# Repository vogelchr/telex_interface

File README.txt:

PCB to implement the interface described here:

https://github.com/fablab-wue/piTelex/wiki/SW_DevRPiTTY

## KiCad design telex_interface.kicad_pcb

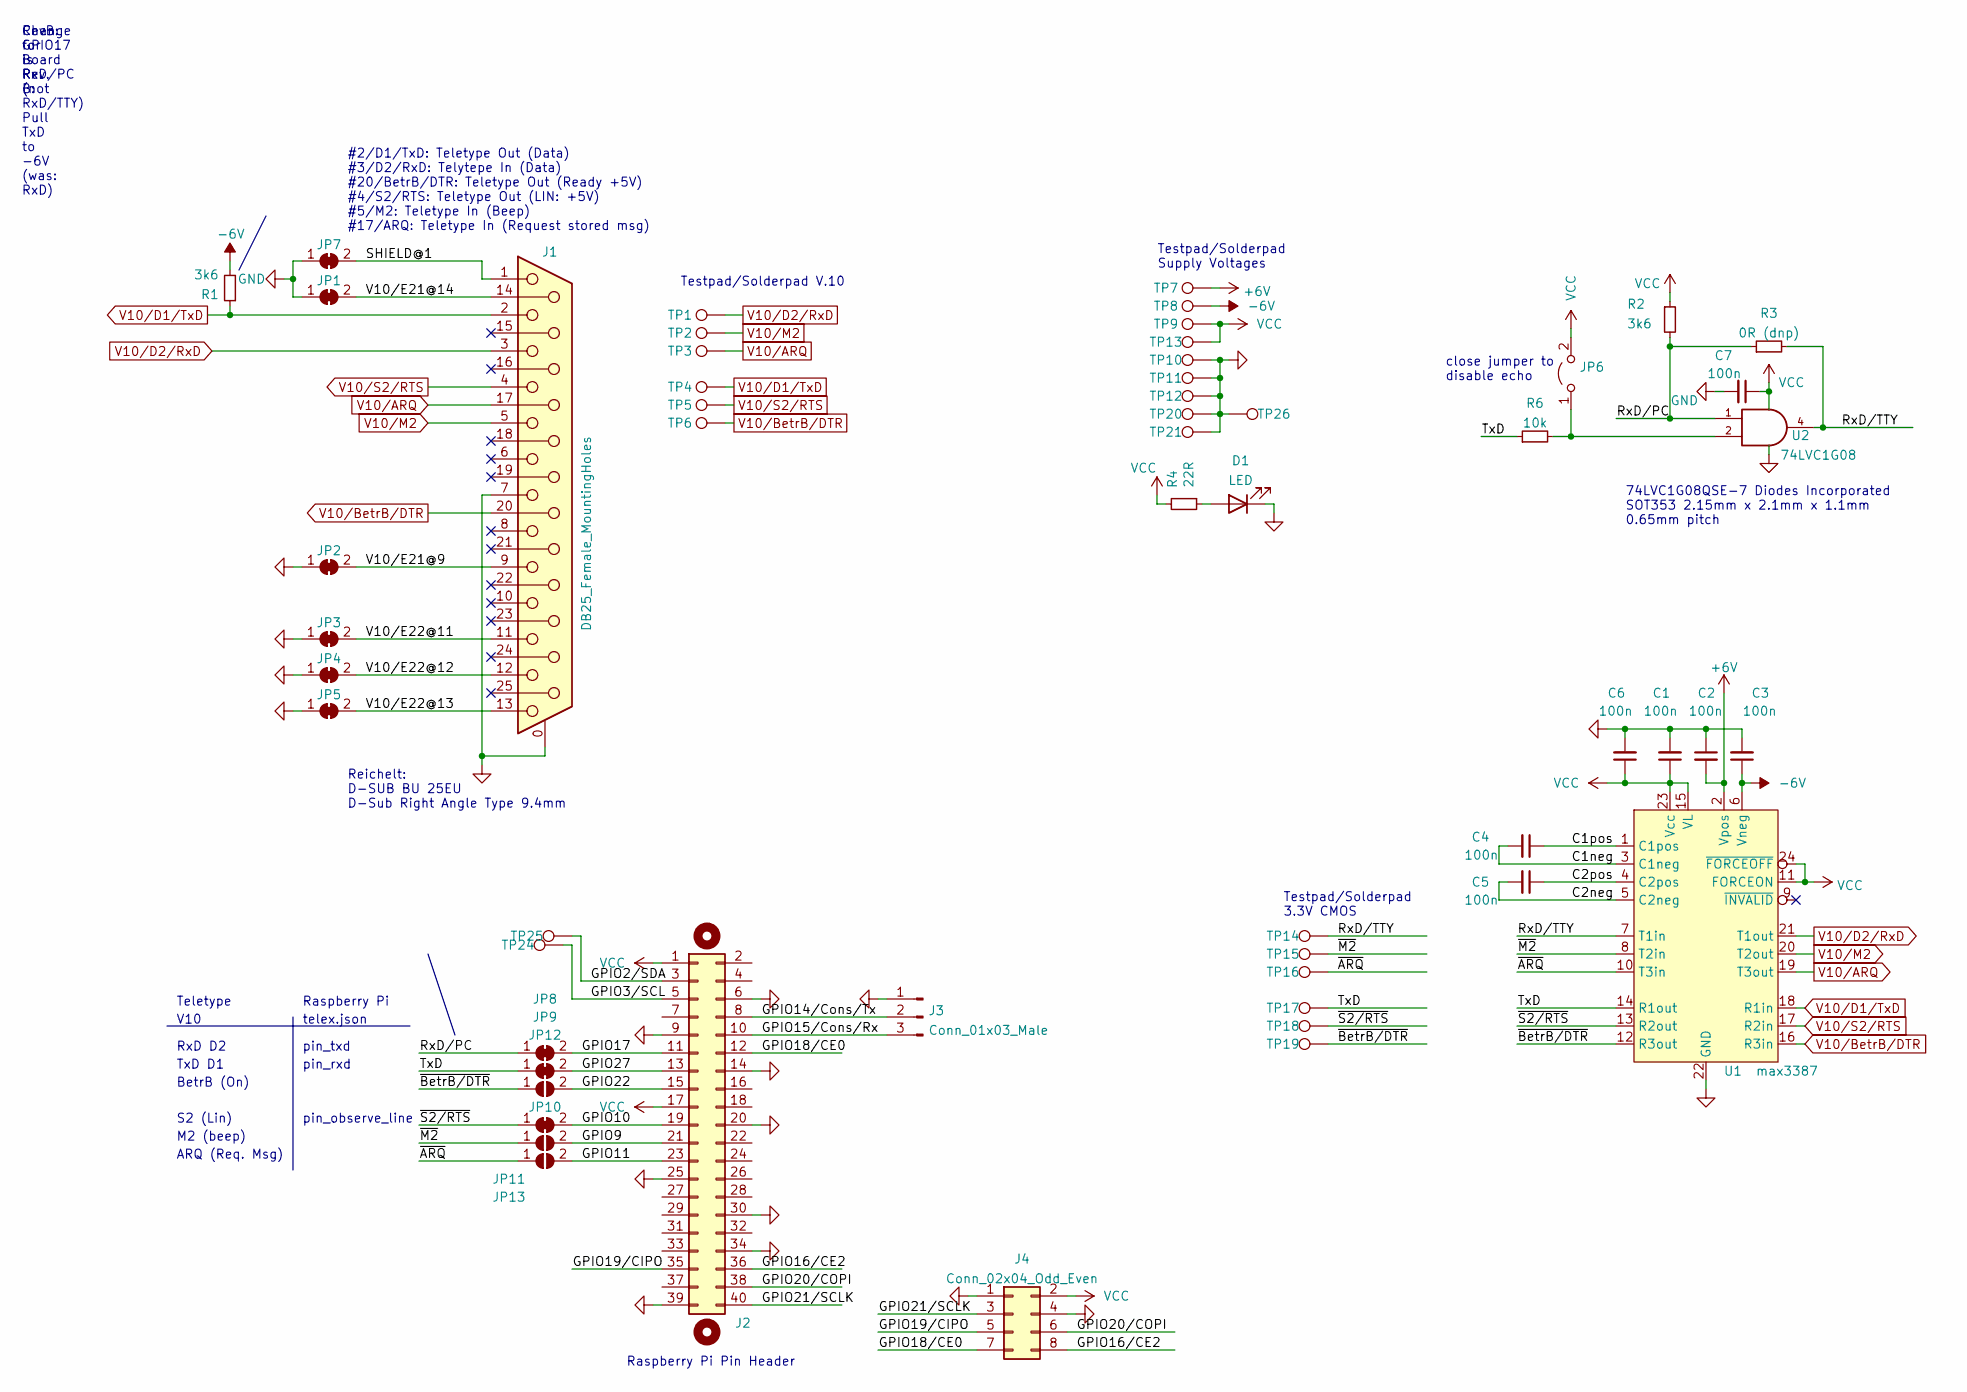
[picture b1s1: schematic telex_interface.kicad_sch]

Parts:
C1, C2, C3, C4, C5, C6, C7: 100n; C_0603_1608Metric
D1: LED; LED_0603_1608Metric
H1, H2: MountingHole; MountingHole_2.7mm_M2.5
J1: DB25_Female_MountingHoles; DSUB-25_Female_Horizontal_P2.77x2.84mm_EdgePinOffset9.90mm_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
J2: Conn_02x20_Odd_Even; PinSocket_2x20_P2.54mm_Vertical
J3: Conn_01x03_Male; PinHeader_1x03_P2.54mm_Vertical
J4: Conn_02x04_Odd_Even; PinHeader_2x04_P2.54mm_Vertical
JP1, JP2, JP3, JP4, JP5, JP7, JP8, JP9, JP10: SolderJumper_2_Bridged; SolderJumper-2_P1.3mm_Bridged_Pad1.0x1.5mm
JP6: Jumper_2_Open; PinHeader_2x01_P2.54mm_Vertical
JP11, JP12, JP13: SolderJumper_2_Open; SolderJumper-2_P1.3mm_Open_Pad1.0x1.5mm
R1, R2: 3k6; R_0603_1608Metric
R3: 0R (dnp); R_0603_1608Metric
R4: 22R; R_0603_1608Metric
R6: 10k; R_0603_1608Metric
TP1, TP2, TP3, TP4, TP5, TP6, TP7, TP8, TP9, TP10, TP11, TP12, TP13, TP14, TP15, TP16, TP17, TP18, TP19, TP20, TP21, TP24, TP25, TP26: TestPoint; TestPoint_Pad_2.0x2.0mm
U1: max3387; TSSOP-24_4.4x7.8mm_P0.65mm
U2: 74LVC1G08; SOT-353_SC-70-5

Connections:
+6V: C2.2, TP7.1, U1.2 (Vpos)
-6V: C3.1, R1.2, TP8.1, U1.6 (Vneg)
/C1neg: C4.2, U1.3 (C1neg)
/C1pos: C4.1, U1.1 (C1pos)
/C2neg: C5.2, U1.5 (C2neg)
/C2pos: C5.1, U1.4 (C2pos)
/GPIO2/SDA: J2.3, TP25.1
/GPIO3/SCL: J2.5, TP24.1
/GPIO9: J2.21, JP11.2 (B)
/GPIO10: J2.19, JP10.2 (B)
/GPIO11: J2.23, JP13.2 (B)
/GPIO14/Cons/Tx: J2.8, J3.2
/GPIO15/Cons/Rx: J2.10, J3.3
/GPIO16/CE2: J2.36, J4.8
/GPIO17: J2.11, JP8.2 (B)
/GPIO18/CE0: J2.12, J4.7
/GPIO19/CIPO: J2.35, J4.5
/GPIO20/COPI: J2.38, J4.6
/GPIO21/SCLK: J2.40, J4.3
/GPIO22: J2.15, JP12.2 (B)
/GPIO27: J2.13, JP9.2 (B)
/RxD/TTY: R3.2, TP14.1, U1.7 (T1in), U2.4
/SHIELD@1: J1.1, JP7.2 (B)
/TxD: JP9.1 (A), R6.1, TP17.1, U1.14 (R1out)
/V10/E21@9: J1.9, JP2.2 (B)
/V10/E21@14: J1.14, JP1.2 (B)
/V10/E22@11: J1.11, JP3.2 (B)
/V10/E22@12: J1.12, JP4.2 (B)
/V10/E22@13: J1.13, JP5.2 (B)
/~ARQ: JP13.1 (A), TP16.1, U1.10 (T3in)
/~BetrB/DTR: JP12.1 (A), TP19.1, U1.12 (R3out)
/~M2: JP11.1 (A), TP15.1, U1.8 (T2in)
/~S2/RTS: JP10.1 (A), TP18.1, U1.13 (R2out)
GND: C1.2, C2.1, C3.2, C6.2, C7.2, D1.1 (K), J1.0 (PAD), J1.7, J2.6, J2.9, J2.14, J2.20, J2.25, J2.30, J2.34, J2.39, J3.1, J4.1, J4.4, JP1.1 (A), JP2.1 (A), JP3.1 (A), JP4.1 (A), JP5.1 (A), JP7.1 (A), TP10.1, TP11.1, TP12.1, TP20.1, TP21.1, TP26.1, U1.22 (GND), U2.3 (GND)
unnamed: D1.2 (A), R4.1
unnamed: JP6.1 (A), R6.2, U2.2
V10/ARQ: J1.17, TP3.1, U1.19 (T3out)
V10/BetrB/DTR: J1.20, TP6.1, U1.16 (R3in)
V10/D1/TxD: J1.2, R1.1, TP4.1, U1.18 (R1in)
V10/D2/RxD: J1.3, TP1.1, U1.21 (T1out)
V10/M2: J1.5, TP2.1, U1.20 (T2out)
V10/S2/RTS: J1.4, TP5.1, U1.17 (R2in)
VCC: C1.1, C6.1, C7.1, J2.1, J2.17, J4.2, JP6.2 (B), R2.1, R4.2, TP9.1, TP13.1, U1.11 (FORCEON), U1.15 (VL), U1.23 (Vcc), U1.24 (~FORCEOFF), U2.5 (VCC)

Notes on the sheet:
RevB: GPIO17 is RxD/PC (not RxD/TTY)
Change for Board Rev. B: Pull TxD to -6V (was: RxD)
RxD D2
V10
TxD D1
Raspberry Pi Pin Header
74LVC1G08QSE-7 Diodes Incorporated SOT353 2.15mm x 2.1mm x 1.1mm 0.65mm pitch
ARQ (Req. Msg)
pin_observe_line
pin_rxd
#2/D1/TxD: Teletype Out (Data) #3/D2/RxD: Telytepe In (Data) #20/BetrB/DTR: Teletype Out (Ready +5V) #4/S2/RTS: Teletype Out (LIN: +5V) #5/M2: Teletype In (Beep) #17/ARQ: Teletype In (Request stored msg)
Testpad/Solderpad Supply Voltages
Raspberry Pi
S2 (Lin)
close jumper to disable echo
pin_txd
M2 (beep)
telex.json
Reichelt: D-SUB BU 25EU D-Sub Right Angle Type 9.4mm
Testpad/Solderpad 3.3V CMOS
Teletype
BetrB (On)
Testpad/Solderpad V.10

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
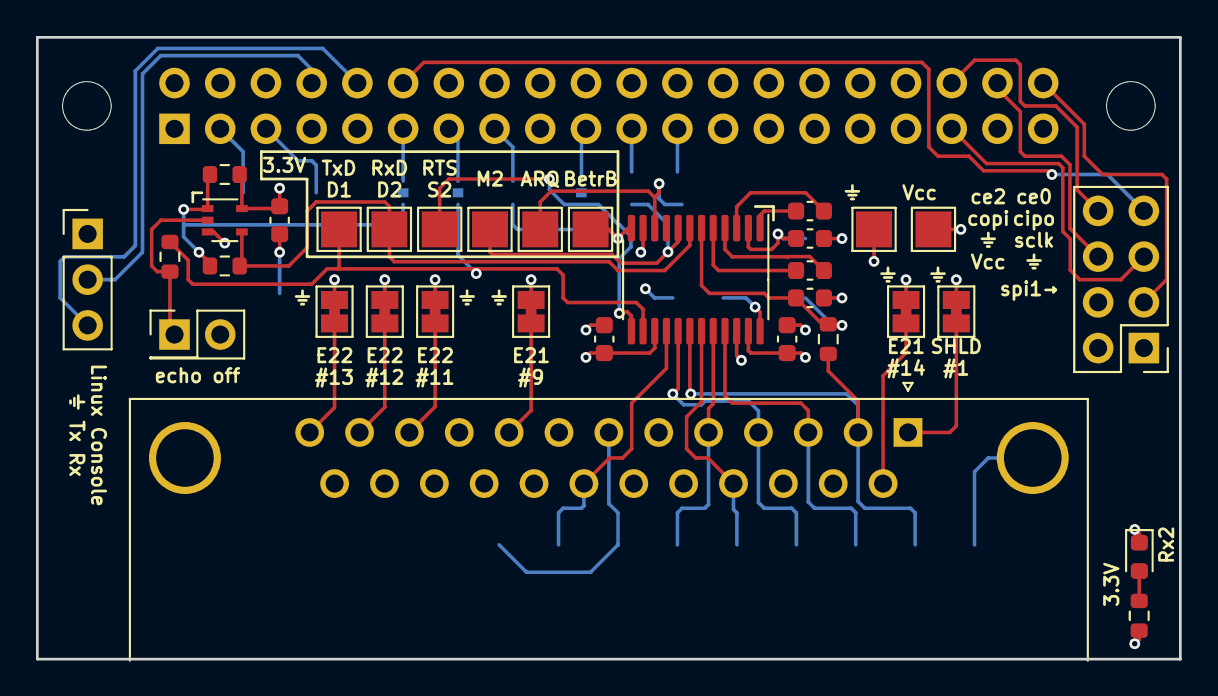
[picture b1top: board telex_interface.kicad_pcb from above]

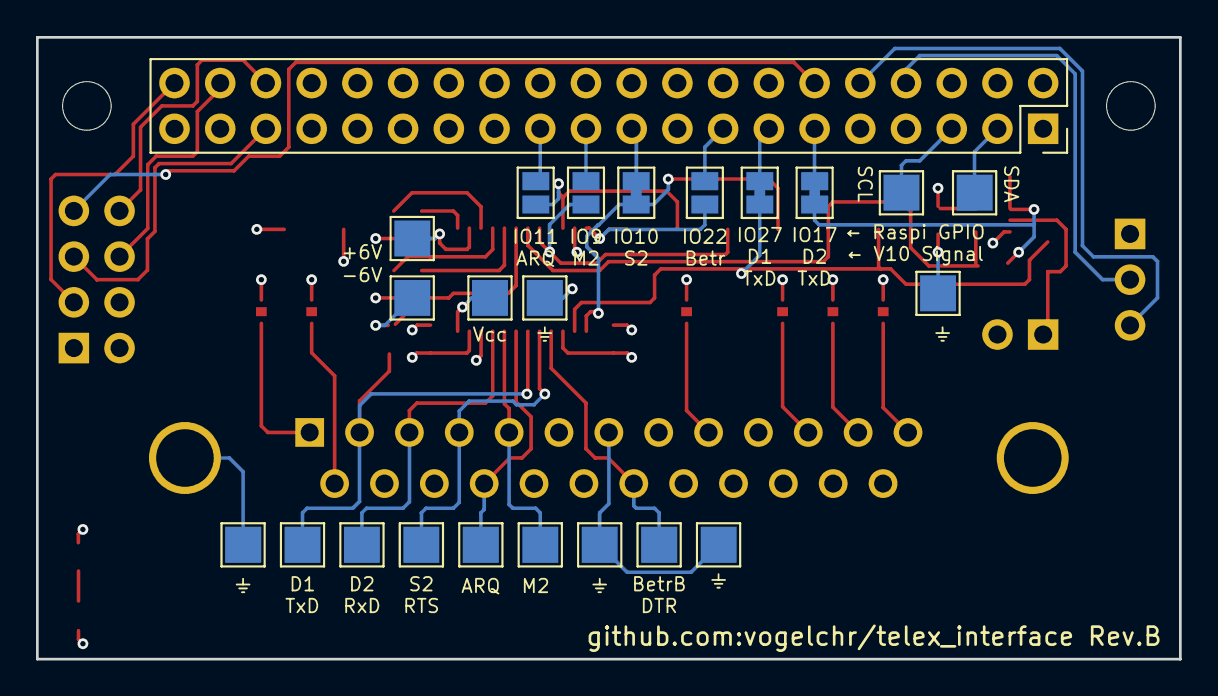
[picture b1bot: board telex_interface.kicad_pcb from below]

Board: 4 copper layers, 63.5 x 34.5 mm, 58 parts (23 on the bottom side), 44 nets.

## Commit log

2021-11-13 Initially empty repository.
2021-11-13 Manual for FS200 added.
2021-11-13 manuals: ITU Recommendation V.10
2021-11-13 Kicad files + .gitignore
2021-11-13 NAND gate for half dumplex echo and pullups
2021-11-13 more work
2021-11-13 PDF of schematic as of 2021-11-13
2021-11-13 add power led
2021-11-14 Add Raspi header.
2021-11-19 removed USB again, made smaller
2021-11-21 moar work
2021-12-04 add #autosave to .gitignore
2021-12-04 Further work...
2022-01-30 Remove _ from labels.
2022-01-30 Changes needed for kicad 5.99 - 6.99
    Fix alignment issue in schematic.
    Newly introduced warning about silkscreen width/text height:
    - change design rules to match what was already successfully produced
    Because of rounding issues (I guess, moving traces by 1 pixel or so
    makes DRC pass) I turned off "soldermask aperture over traces with
    different nets".
2022-01-30 Fix mistakes made during first spin of board (RevA):
    R1 Pulldown to -6V was on RxD (input of TTY, output of maxim driver)
    instead of TxD (output of TTY, input of maxim driver).
    ==> moved to V10/D1/TxD signal, Pin 2 of DSUB
    Raspi GPIO17 was on net RxD/TTY (output of the single gate buffer U2)
    instead of net RxD/PC (input to U2), so both outputs (raspi & U2) were
    on the same net.
2022-01-30 Add README.
